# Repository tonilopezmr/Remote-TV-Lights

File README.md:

# Remote-TV-Lights
Turn on/off TV Leds with remote control.

Board supplied by USB from TV which turns on/off DC 12v LEDs by NPN Transistor TIP41C remotely using any remote control. 

### Usage
You need to configure it for add allowed infrared signals clicking to the button, then the led starts blinking, that means the board it is waiting to get an infrared signal from your remote control, then press to the remote control button you selected for turn on/off TV lights, once you have pressed the button and the led stop blinking the board has been configured, just press the button to check your light is turning on/off.

### PCB 

Top layout

Bottom layout

## Open Hardware

Hardware designs (schematics and CAD) files are licensed under the [Creative Commons Attribution-ShareAlike 3.0 Unported License](http://creativecommons.org/licenses/by-sa/3.0/) and follow the terms of the [OSHW (Open-source hardware) Statement of Principles 1.0.](http://freedomdefined.org/OSHW)

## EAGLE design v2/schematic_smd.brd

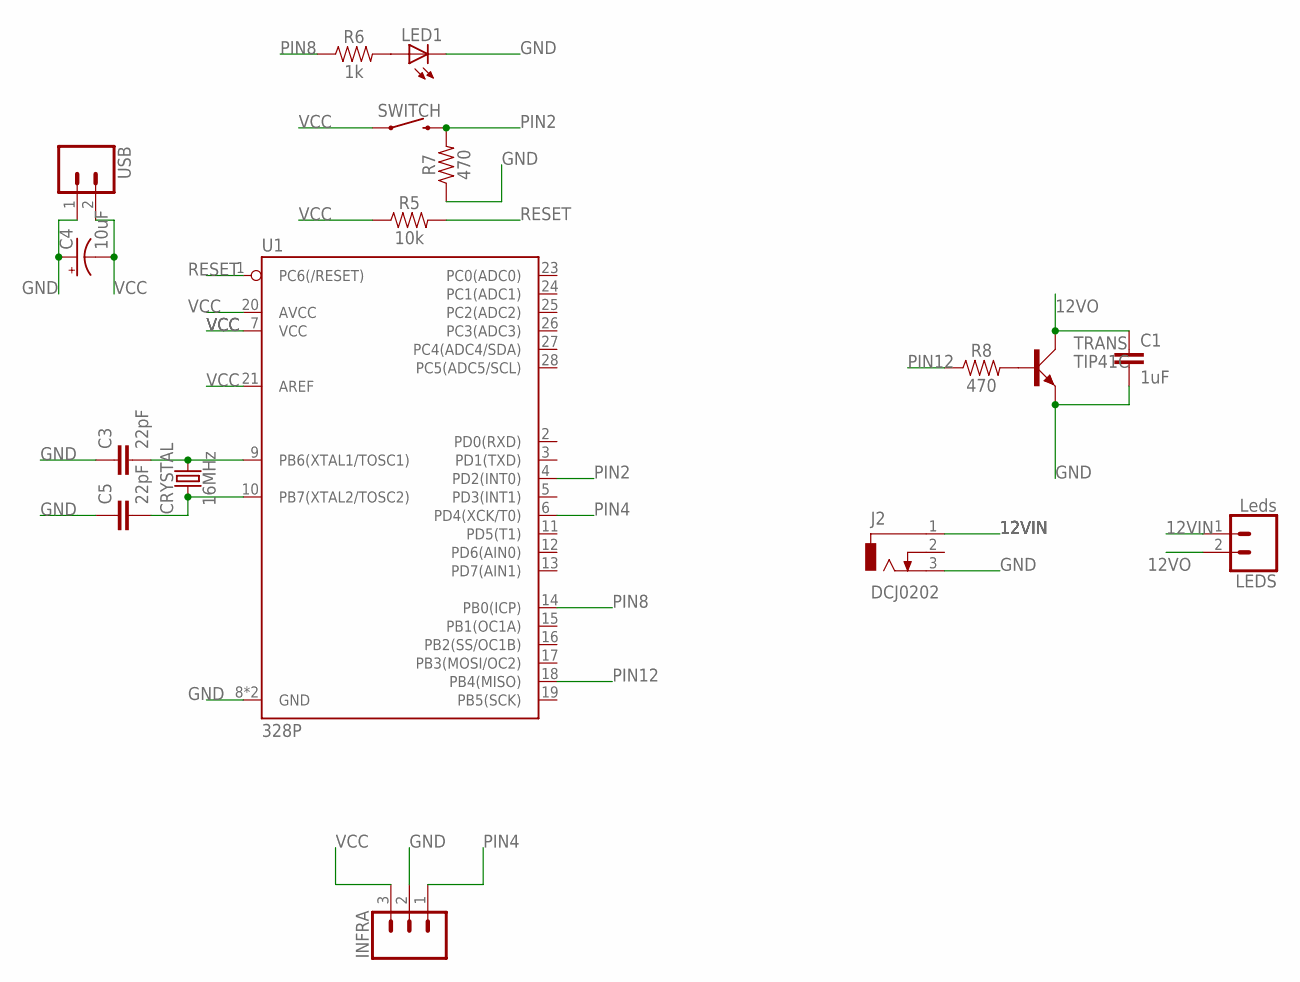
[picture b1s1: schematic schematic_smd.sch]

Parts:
C1: 1uF; 1206
C3, C5: 22pF; 1206
C4: 10uF; CPOL-RADIAL-2.5MM-5MM
CRYSTAL: 16MHz; HC49US
INFRA: 455-1750-1-ND; 1X03
J2: DCJ0202
LED1: LED5MM
LEDS: Leds; JST-2-PTH-KIT
R5: 10k; 0805
R6: 1k; 1206
R7, R8: 470; 1206
SWITCH: MOMENTARY-SWITCH-SPST-PTH-6.0MM; TACTILE_SWITCH_PTH_6.0MM
TRANS: TIP41C; TO220AV
U1: 328P; DIP28
USB: CONN_02JST-PTH-2-KIT; JST-2-PTH-KIT

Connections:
12VIN: J2.1, LEDS.1
12VO: C1.1, LEDS.2, TRANS.C
GND: C1.2, C3.1, C4.1 (+), C5.1, INFRA.2, J2.3, LED1.K (C), R7.1, TRANS.E, U1.8 (GND), U1.22 (GND), USB.1
unnamed: C5.2, CRYSTAL.1, U1.10 (PB7(XTAL2/TOSC2))
unnamed: C3.2, CRYSTAL.2, U1.9 (PB6(XTAL1/TOSC1))
unnamed: LED1.A, R6.2
unnamed: R8.2, TRANS.B
PIN2: R7.2, SWITCH.3 (2), U1.4 (PD2(INT0))
PIN4: INFRA.1, U1.6 (PD4(XCK/T0))
PIN8: R6.1, U1.14 (PB0(ICP))
PIN12: R8.1, U1.18 (PB4(MISO))
RESET: R5.2, U1.1 (PC6(/RESET))
VCC: C4.2 (-), INFRA.3, R5.1, SWITCH.1, U1.7 (VCC), U1.20 (AVCC), U1.21 (AREF), USB.2

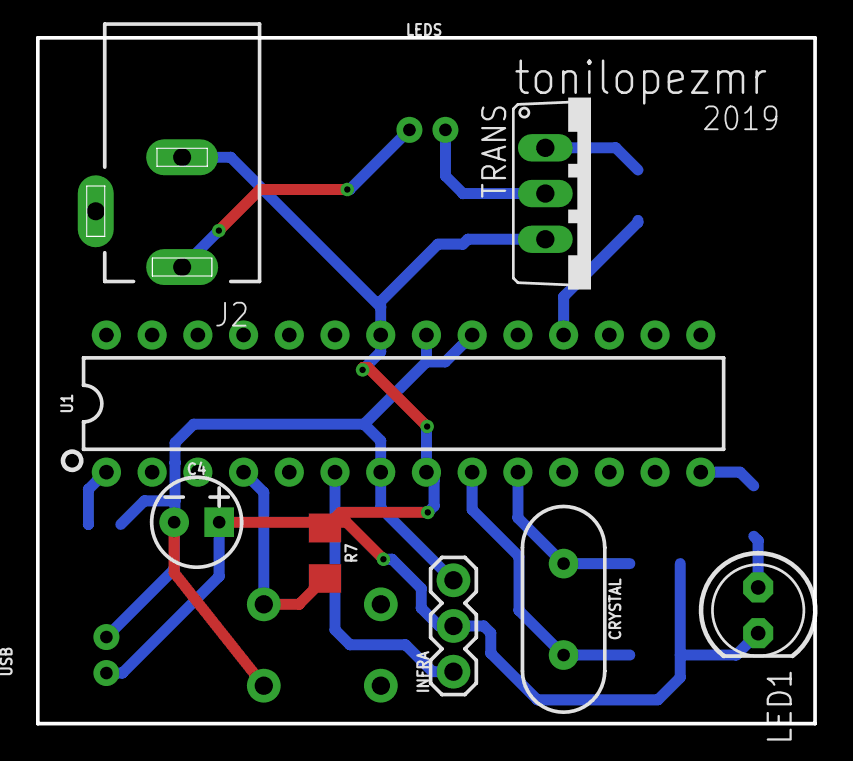
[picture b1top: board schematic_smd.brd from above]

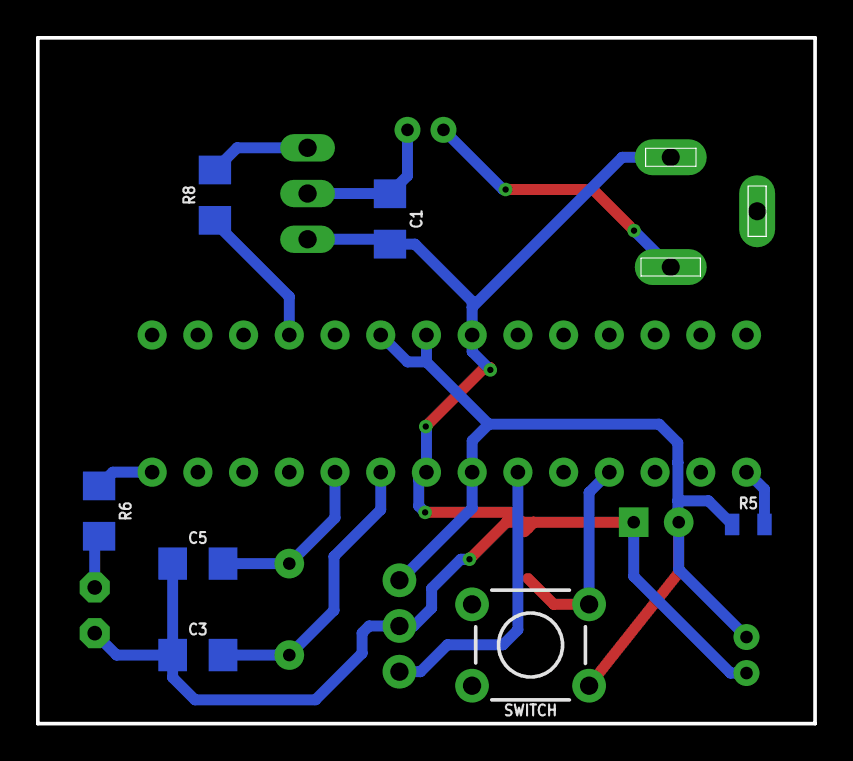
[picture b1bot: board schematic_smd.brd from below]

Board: 2 copper layers, 43.2 x 38.1 mm, 17 parts (7 on the bottom side), 13 nets.

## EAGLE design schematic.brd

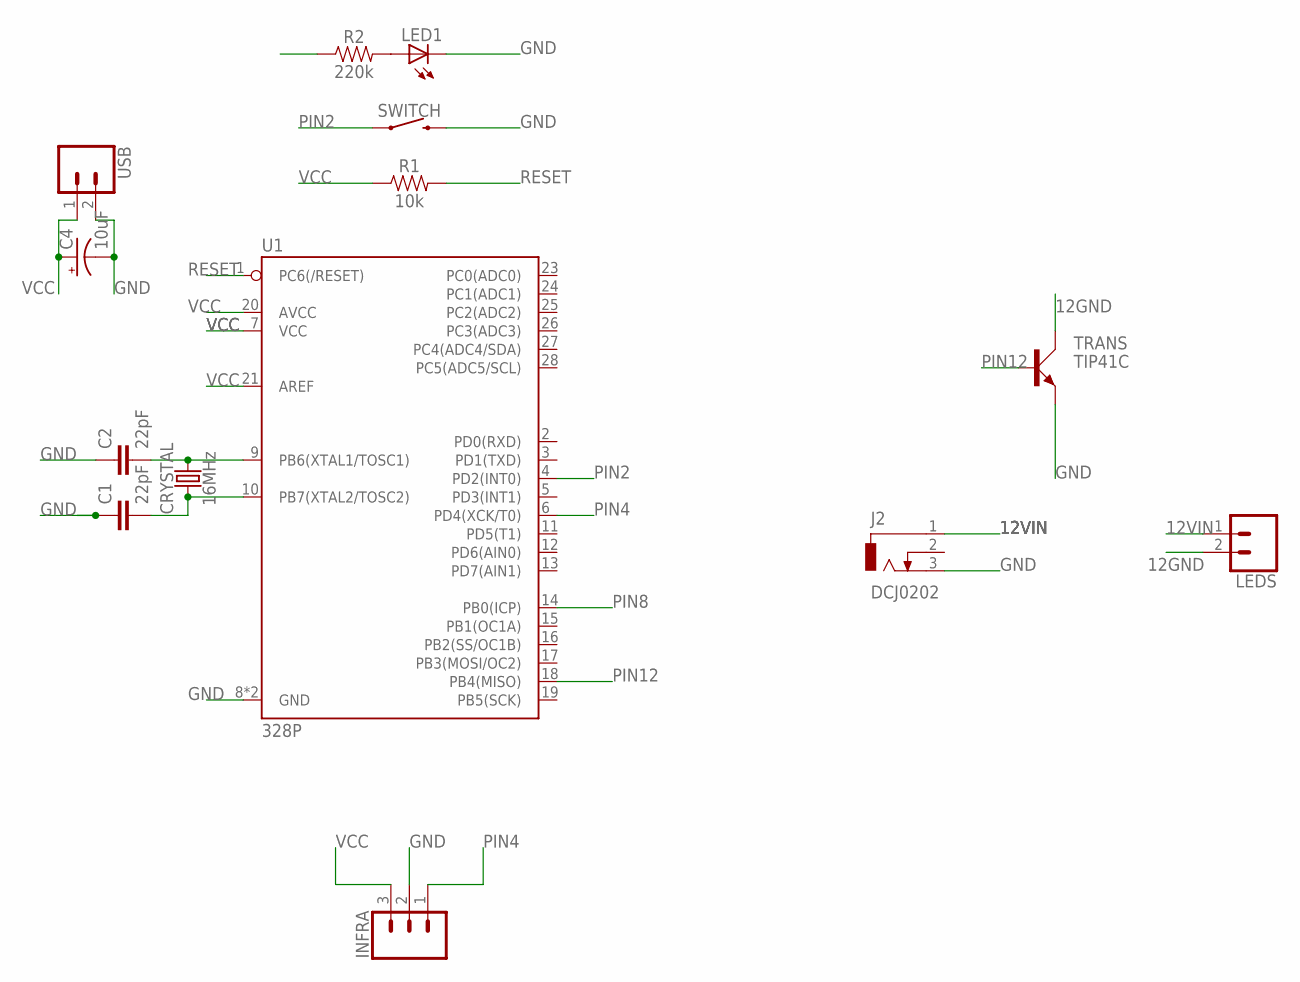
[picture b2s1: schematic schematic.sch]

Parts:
C1, C2: 22pF; CAP-PTH-2.54
C4: 10uF; CPOL-RADIAL-2.5MM-5MM
CRYSTAL: 16MHz; HC49US
INFRA: 455-1750-1-ND; 1X03
J2: DCJ0202
LED1: LED5MM
LEDS: CONN_02; 1X02
R1: 10k; AXIAL-0.3
R2: 220k; AXIAL-0.3
SWITCH: MOMENTARY-SWITCH-SPST-PTH-6.0MM; TACTILE_SWITCH_PTH_6.0MM
TRANS: TIP41C; TO220AV
U1: 328P; DIP28
USB: CONN_02; 1X02

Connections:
12GND: LEDS.2, TRANS.C
12VIN: J2.1, LEDS.1
GND: C1.1, C2.1, C4.2 (-), INFRA.2, J2.3, LED1.K (C), SWITCH.3 (2), TRANS.E, U1.8 (GND), U1.22 (GND), USB.2
unnamed: C1.2, CRYSTAL.1, U1.10 (PB7(XTAL2/TOSC2))
unnamed: C2.2, CRYSTAL.2, U1.9 (PB6(XTAL1/TOSC1))
unnamed: LED1.A, R2.P$2 (2)
PIN2: SWITCH.1, U1.4 (PD2(INT0))
PIN4: INFRA.1, U1.6 (PD4(XCK/T0))
PIN8: R2.P$1 (1), U1.14 (PB0(ICP))
PIN12: TRANS.B, U1.18 (PB4(MISO))
RESET: R1.P$2 (2), U1.1 (PC6(/RESET))
VCC: C4.1 (+), INFRA.3, R1.P$1 (1), U1.7 (VCC), U1.20 (AVCC), U1.21 (AREF), USB.1

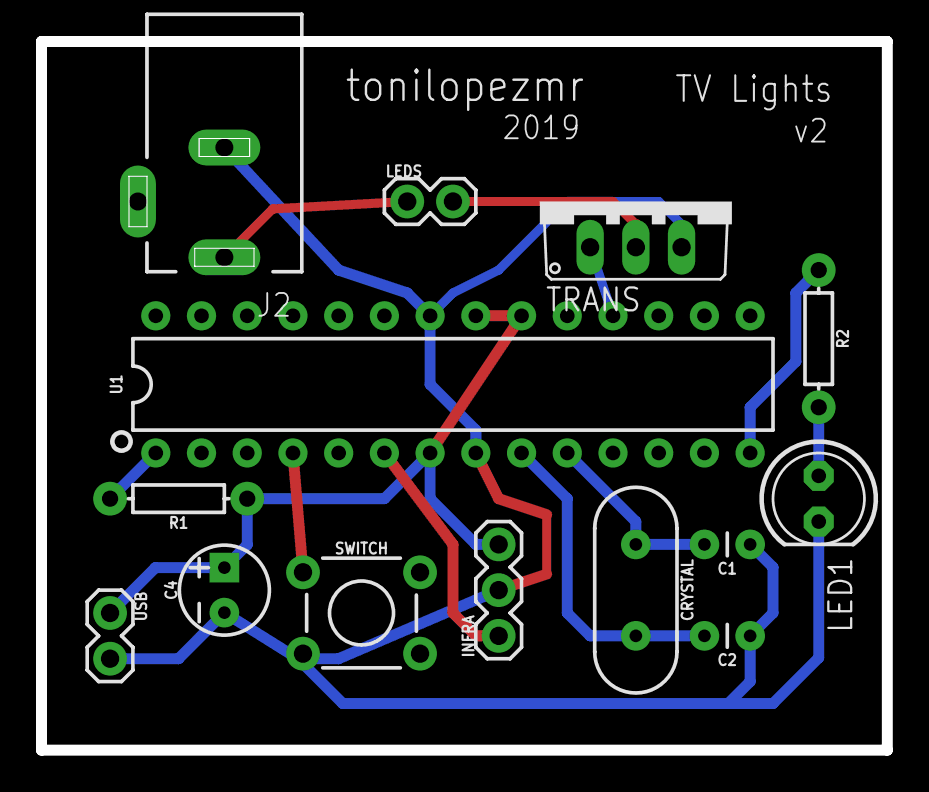
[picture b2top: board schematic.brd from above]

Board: 2 copper layers, 47.0 x 39.4 mm, 14 parts (0 on the bottom side), 12 nets.

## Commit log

2019-03-25 Add project v2
2019-03-25 Create manufacturer folder
2019-03-25 V2 project
2019-03-25 Add pictures to README and adding firmware
2019-03-25 Add usage section
2019-03-25 Add v1 enclosure
2019-03-25 Move firmware to v1
2019-04-29 Added v2 smd board
2019-10-10 refactor ws and add html
2019-10-10 refactor ws and add html (#1)
2019-10-10 Software folder
2019-10-12 Wifi working
2019-10-12 Now can modify css
2019-10-12 Add board name and relay button
2019-10-13 Finished
2019-10-13 Working version
2019-10-14 Remove unnecessary css
2019-10-15 Optimization (#2)
    * Finished
    * Working version
    * Remove unnecessary css
2019-11-19 Improve
2020-04-05 Bump acorn from 6.3.0 to 6.4.1 in /software/html
    Bumps [acorn](https://github.com/acornjs/acorn) from 6.3.0 to 6.4.1.
    - [Release notes](https://github.com/acornjs/acorn/releases)
    - [Commits](https://github.com/acornjs/acorn/compare/6.3.0...6.4.1)
2020-06-07 Bump websocket-extensions from 0.1.3 to 0.1.4 in /software/html
    Bumps [websocket-extensions](https://github.com/faye/websocket-extensions-node) from 0.1.3 to 0.1.4.
    - [Release notes](https://github.com/faye/websocket-extensions-node/releases)
    - [Changelog](https://github.com/faye/websocket-extensions-node/blob/master/CHANGELOG.md)
    - [Commits](https://github.com/faye/websocket-extensions-node/compare/0.1.3...0.1.4)
2020-07-18 Bump lodash from 4.17.15 to 4.17.19 in /software/html
    Bumps [lodash](https://github.com/lodash/lodash) from 4.17.15 to 4.17.19.
    - [Release notes](https://github.com/lodash/lodash/releases)
    - [Commits](https://github.com/lodash/lodash/compare/4.17.15...4.17.19)
2020-07-31 Bump elliptic from 6.5.1 to 6.5.3 in /software/html
    Bumps [elliptic](https://github.com/indutny/elliptic) from 6.5.1 to 6.5.3.
    - [Release notes](https://github.com/indutny/elliptic/releases)
    - [Commits](https://github.com/indutny/elliptic/compare/v6.5.1...v6.5.3)
2020-09-10 Bump http-proxy from 1.18.0 to 1.18.1 in /software/html
    Bumps [http-proxy](https://github.com/http-party/node-http-proxy) from 1.18.0 to 1.18.1.
    - [Release notes](https://github.com/http-party/node-http-proxy/releases)
    - [Changelog](https://github.com/http-party/node-http-proxy/blob/master/CHANGELOG.md)
    - [Commits](https://github.com/http-party/node-http-proxy/compare/1.18.0...1.18.1)
2020-12-11 Bump ini from 1.3.5 to 1.3.8 in /software/html
    Bumps [ini](https://github.com/isaacs/ini) from 1.3.5 to 1.3.8.
    - [Release notes](https://github.com/isaacs/ini/releases)
    - [Commits](https://github.com/isaacs/ini/compare/v1.3.5...v1.3.8)
2021-03-09 Bump elliptic from 6.5.1 to 6.5.4 in /software/html
    Bumps [elliptic](https://github.com/indutny/elliptic) from 6.5.1 to 6.5.4.
    - [Release notes](https://github.com/indutny/elliptic/releases)
    - [Commits](https://github.com/indutny/elliptic/compare/v6.5.1...v6.5.4)
2021-03-31 Bump y18n from 4.0.0 to 4.0.1 in /software/html
    Bumps [y18n](https://github.com/yargs/y18n) from 4.0.0 to 4.0.1.
    - [Release notes](https://github.com/yargs/y18n/releases)
    - [Changelog](https://github.com/yargs/y18n/blob/master/CHANGELOG.md)
    - [Commits](https://github.com/yargs/y18n/commits)
2021-04-30 Bump ssri from 6.0.1 to 6.0.2 in /software/html
    Bumps [ssri](https://github.com/npm/ssri) from 6.0.1 to 6.0.2.
    - [Release notes](https://github.com/npm/ssri/releases)
    - [Changelog](https://github.com/npm/ssri/blob/v6.0.2/CHANGELOG.md)
    - [Commits](https://github.com/npm/ssri/compare/v6.0.1...v6.0.2)
2021-05-08 Bump url-parse from 1.4.7 to 1.5.1 in /software/html
    Bumps [url-parse](https://github.com/unshiftio/url-parse) from 1.4.7 to 1.5.1.
    - [Release notes](https://github.com/unshiftio/url-parse/releases)
    - [Commits](https://github.com/unshiftio/url-parse/compare/1.4.7...1.5.1)
2021-05-10 Bump lodash from 4.17.15 to 4.17.21 in /software/html
    Bumps [lodash](https://github.com/lodash/lodash) from 4.17.15 to 4.17.21.
    - [Release notes](https://github.com/lodash/lodash/releases)
    - [Commits](https://github.com/lodash/lodash/compare/4.17.15...4.17.21)
2021-05-28 Bump dns-packet from 1.3.1 to 1.3.4 in /software/html
    Bumps [dns-packet](https://github.com/mafintosh/dns-packet) from 1.3.1 to 1.3.4.
    - [Release notes](https://github.com/mafintosh/dns-packet/releases)
    - [Changelog](https://github.com/mafintosh/dns-packet/blob/master/CHANGELOG.md)
    - [Commits](https://github.com/mafintosh/dns-packet/compare/v1.3.1...v1.3.4)
2021-05-29 Bump ws from 7.1.2 to 7.4.6 in /software/html/test_server
    Bumps [ws](https://github.com/websockets/ws) from 7.1.2 to 7.4.6.
    - [Release notes](https://github.com/websockets/ws/releases)
    - [Commits](https://github.com/websockets/ws/compare/7.1.2...7.4.6)
2021-05-29 Bump ws from 7.1.2 to 7.4.6 in /software/html
    Bumps [ws](https://github.com/websockets/ws) from 7.1.2 to 7.4.6.
    - [Release notes](https://github.com/websockets/ws/releases)
    - [Commits](https://github.com/websockets/ws/compare/7.1.2...7.4.6)
2021-10-06 Bump url-parse from 1.4.7 to 1.5.3 in /software/html
    Bumps [url-parse](https://github.com/unshiftio/url-parse) from 1.4.7 to 1.5.3.
    - [Release notes](https://github.com/unshiftio/url-parse/releases)
    - [Commits](https://github.com/unshiftio/url-parse/compare/1.4.7...1.5.3)
    ---
    updated-dependencies:
    - dependency-name: url-parse
2022-01-13 Bump follow-redirects from 1.9.0 to 1.14.7 in /software/html
    Bumps [follow-redirects](https://github.com/follow-redirects/follow-redirects) from 1.9.0 to 1.14.7.
    - [Release notes](https://github.com/follow-redirects/follow-redirects/releases)
    - [Commits](https://github.com/follow-redirects/follow-redirects/compare/v1.9.0...v1.14.7)
    ---
    updated-dependencies:
    - dependency-name: follow-redirects
2022-02-12 Bump ajv from 6.10.2 to 6.12.6 in /software/html
    Bumps [ajv](https://github.com/ajv-validator/ajv) from 6.10.2 to 6.12.6.
    - [Release notes](https://github.com/ajv-validator/ajv/releases)
    - [Commits](https://github.com/ajv-validator/ajv/compare/v6.10.2...v6.12.6)
    ---
    updated-dependencies:
    - dependency-name: ajv
2022-02-12 Bump follow-redirects from 1.9.0 to 1.14.8 in /software/html
    Bumps [follow-redirects](https://github.com/follow-redirects/follow-redirects) from 1.9.0 to 1.14.8.
    - [Release notes](https://github.com/follow-redirects/follow-redirects/releases)
    - [Commits](https://github.com/follow-redirects/follow-redirects/compare/v1.9.0...v1.14.8)
    ---
    updated-dependencies:
    - dependency-name: follow-redirects
2022-02-18 Bump url-parse from 1.4.7 to 1.5.7 in /software/html
    Bumps [url-parse](https://github.com/unshiftio/url-parse) from 1.4.7 to 1.5.7.
    - [Release notes](https://github.com/unshiftio/url-parse/releases)
    - [Commits](https://github.com/unshiftio/url-parse/compare/1.4.7...1.5.7)
    ---
    updated-dependencies:
    - dependency-name: url-parse
2022-02-26 Bump url-parse from 1.4.7 to 1.5.10 in /software/html
    Bumps [url-parse](https://github.com/unshiftio/url-parse) from 1.4.7 to 1.5.10.
    - [Release notes](https://github.com/unshiftio/url-parse/releases)
    - [Commits](https://github.com/unshiftio/url-parse/compare/1.4.7...1.5.10)
    ---
    updated-dependencies:
    - dependency-name: url-parse
2022-06-01 Bump eventsource from 1.0.7 to 1.1.1 in /software/html
    Bumps [eventsource](https://github.com/EventSource/eventsource) from 1.0.7 to 1.1.1.
    - [Release notes](https://github.com/EventSource/eventsource/releases)
    - [Changelog](https://github.com/EventSource/eventsource/blob/master/HISTORY.md)
    - [Commits](https://github.com/EventSource/eventsource/compare/v1.0.7...v1.1.1)
    ---
    updated-dependencies:
2022-07-20 Bump terser from 4.3.8 to 4.8.1 in /software/html
    Bumps [terser](https://github.com/terser/terser) from 4.3.8 to 4.8.1.
    - [Release notes](https://github.com/terser/terser/releases)
    - [Changelog](https://github.com/terser/terser/blob/master/CHANGELOG.md)
    - [Commits](https://github.com/terser/terser/commits)
    ---
    updated-dependencies:
2022-11-08 Bump loader-utils and webpack-cli in /software/html
    Bumps [loader-utils](https://github.com/webpack/loader-utils) to 1.4.1 and updates ancestor dependency [webpack-cli](https://github.com/webpack/webpack-cli). These dependencies need to be updated tog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
    Updates `loader-utils` from 1.2.3 to 1.4.1
    - [Release notes](https://github.com/webpack/loader-utils/releases)
    - [Changelog](https://github.com/webpack/loader-utils/blob/v1.4.1/CHANGELOG.md)
    - [Commits](https://github.com/webpack/loader-utils/compare/v1.2.3...v1.4.1)
    Updates `webpack-cli` from 3.3.9 to 3.3.12
2022-11-18 Bump loader-utils and webpack-cli in /software/html
    Bumps [loader-utils](https://github.com/webpack/loader-utils) to 1.4.2 and updates ancestor dependency [webpack-cli](https://github.com/webpack/webpack-cli). These dependencies need to be updated tog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
    Updates `loader-utils` from 1.2.3 to 1.4.2
    - [Release notes](https://github.com/webpack/loader-utils/releases)
    - [Changelog](https://github.com/webpack/loader-utils/blob/v1.4.2/CHANGELOG.md)
    - [Commits](https://github.com/webpack/loader-utils/compare/v1.2.3...v1.4.2)
    Updates `webpack-cli` from 3.3.9 to 3.3.12
2022-12-04 Bump decode-uri-component from 0.2.0 to 0.2.2 in /software/html
    Bumps [decode-uri-component](https://github.com/SamVerschueren/decode-uri-component) from 0.2.0 to 0.2.2.
    - [Release notes](https://github.com/SamVerschueren/decode-uri-component/releases)
    - [Commits](https://github.com/SamVerschueren/decode-uri-component/compare/v0.2.0...v0.2.2)
    ---
    updated-dependencies:
    - dependency-name: decode-uri-component
2022-12-07 Bump qs and express in /software/html
    Bumps [qs](https://github.com/ljharb/qs) and [express](https://github.com/expressjs/express). These dependencies needed to be updated together.
    Updates `qs` from 6.7.0 to 6.11.0
    - [Release notes](https://github.com/ljharb/qs/releases)
    - [Changelog](https://github.com/ljharb/qs/blob/main/CHANGELOG.md)
    - [Commits](https://github.com/ljharb/qs/compare/v6.7.0...v6.11.0)
    Updates `express` from 4.17.1 to 4.18.2
2022-12-11 Bump express from 4.17.1 to 4.18.2 in /software/html
    Bumps [express](https://github.com/expressjs/express) from 4.17.1 to 4.18.2.
    - [Release notes](https://github.com/expressjs/express/releases)
    - [Changelog](https://github.com/expressjs/express/blob/master/History.md)
    - [Commits](https://github.com/expressjs/express/compare/4.17.1...4.18.2)
    ---
    updated-dependencies:

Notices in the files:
parts and their libraries:
SparkFun-Capacitors: Licensing: Creative Commons ShareAlike 4.0 International - https://creativecommons.org/licenses/by-sa/4.0
